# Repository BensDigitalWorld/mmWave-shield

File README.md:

# mmWave-shield

## Wearable mmWave Sensor, for BP measurments. Shield for the BioGap9 Platform 

## Introduction

This repository contains the hardware, firmware, and software developed for a wearable mmWave radar sensing prototype based on the BioGAP platform.

The project integrates a custom BGT60TR13C mmWave radar shield with the BioGAP firmware and provides Python tools for data acquisition, live visualization, offline signal processing, and validation measurements.

The system was developed as a research prototype for contactless pulse-wave sensing using a wearable mmWave radar sensor.

<p align="center">
  <br>
  <em>BioGAP mmWave radar system during validation measurements.</em>
</p>

The prototype includes the following main features:

- Custom mmWave radar shield based on the Infineon BGT60TR13C radar sensor
- Integration with the BioGAP wearable platform
- SPI-based radar control and raw frame readout
- BLE-based command interface and raw radar data streaming
- Python host software for acquisition, live viewing, and offline analysis
- Support for synchronized validation measurements with Finapres/NovaScope reference data
- Mechanical casing files for reproducing the validation setup

## Structure of the Repository

This repository is organized into the following main folders:

```text
Repository/
├── Documentation/
├── Firmware/
├── Hardware/
├── Software/
└── README.md
```

- `Documentation/` contains user documentation, setup instructions, and additional project notes and images.

- `Firmware/` contains the BioGAP firmware extension for the mmWave radar shield. This includes the mmWave application layer, radar control logic, BLE command integration, and firmware configuration changes.

- `Hardware/` contains the hardware design files for the custom mmWave radar shield and the mechanical casing files. This includes KiCad PCB files, fabrication outputs, casing STEP files, and Solid Edge source files.

- `Software/` contains the Python host software for acquisition, live visualization, signal processing, plotting, and validation analysis.

## Usage

For detailed setup and usage instructions, see 

[Getting started FW](Documentation/Firmware/getting_started.md)
[Getting started SW](Software/README.md)

A typical workflow consists of flashing the mmWave firmware, starting the Python host software, recording raw radar data, and processing the measurements offline.

<p align="center">
  <br>
  <em>Python live viewer used to inspect the mmWave radar waveform in real time.</em>
</p>

## Authors

This project was developed at the Integrated Systems Laboratory (IIS) at ETH Zurich.

Main development:

- Benjamin Löliger, ETH Zurich  
  Hardware design, firmware integration, Python software, measurements, signal processing, documentation

Supervision and support:

- Sebastian Frey, ETH Zurich  
  Supervision and project guidance

- Andrea Cossettini, ETH Zurich  
  Supervision and project guidance

- Nima Bahmani, Aalton Finland  
  Supervision and project guidance

## License

The following parts of this repository are released under the Apache License 2.0:

- `Software/`
- `Firmware/`

See the corresponding license files for details: [Software/LICENSE](Software/LICENSE) and [Firmware/LICENSE](Firmware/LICENSE).

The hardware design files are released under the Solderpad Hardware License v0.51:

- `Hardware/`

See [Hardware/LICENSE](Hardware/LICENSE) for details.

This includes the PCB design files as well as the mechanical casing design files, such as STEP and Solid Edge files.

The following documentation images are released under the Creative Commons Attribution 4.0 International License (CC-BY-4.0):

- `Documentation/images/`
- `Hardware/casing/images/`

See the corresponding license files for details: [Documentation/images/LICENSE](Documentation/images/LICENSE) and [Hardware/Casing/images/LICENSE](Hardware/Casing/images/LICENSE).

Some files in the software tools directories contain third-party source code from the Infineon Radar SDK or files based on Infineon example code. Some of these files were adapted for this project.

See the respective source file headers for original copyright notices, modification notes, and license terms.

## Limitation of Liability

The hardware designs, firmware, and software in this repository are provided as-is, without warranty of any kind.

The project is a research prototype and is not intended for medical diagnosis, clinical decision-making, or safety-critical use. The authors and contributors are not liable for any damages or losses arising from the use of this repository, including but not limited to hardware damage, data loss, measurement errors, or incorrect interpretation of results.

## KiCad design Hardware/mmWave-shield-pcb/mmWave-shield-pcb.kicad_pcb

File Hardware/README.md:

# Hardware

## PCB

This directory contains the hardware design files for the custom mmWave radar shield used in this project.

The following PCB project is included:

```text
mmWave-shield-pcb/
```

The PCB was designed in KiCad and contains the schematic, PCB layout, local project libraries, and generated fabrication outputs required to manufacture and assemble the board.

Inside the project folder, you can find the KiCad design files as well as generated documentation and fabrication files such as schematics, bill of materials, Gerber files, and 3D model exports.

## Casing

In the folder Casing you can find .stl files for a 3d printed casing model that can be used with the BioGap + mmWave Shield. 

## License

The hardware source design files are licensed under the Solderpad Hardware License v0.51. See `Hardware/LICENSE` for details.

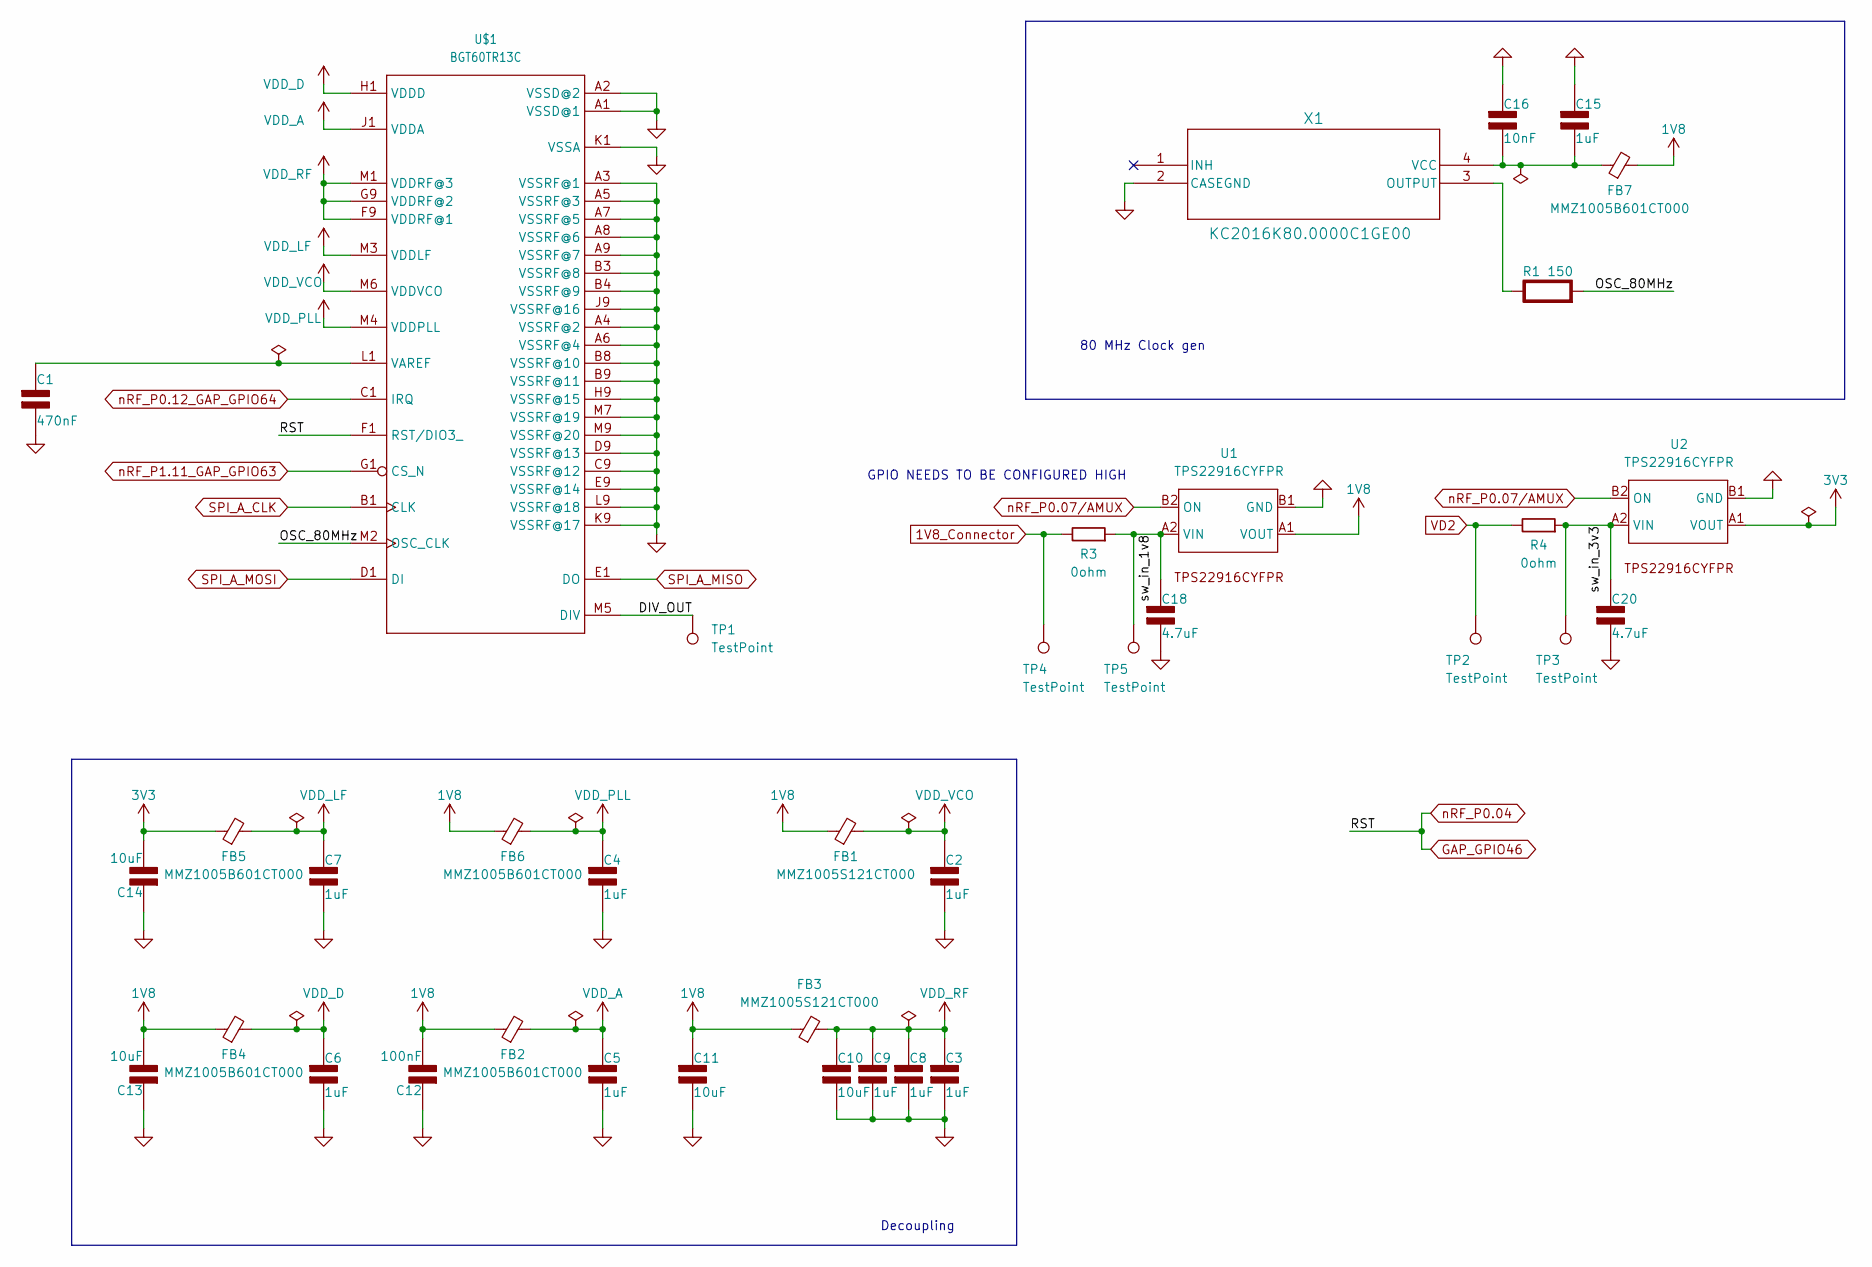
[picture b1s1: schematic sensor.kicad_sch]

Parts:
C1: 470nF; C_0402_1005Metric; Rating V
C2, C3, C4, C5, C6, C7, C8, C9, C15: 1uF; C_0402_1005Metric; Rating V
C10, C11, C13, C14: 10uF; C_0402_1005Metric; Rating V
C12: 100nF; C_0402_1005Metric; Rating V
C16: 10nF; C_0402_1005Metric; Rating V
C18, C20: 4.7uF; C_0402_1005Metric; Rating V
FB1, FB3: MMZ1005S121CT000; IND_1005_TDK-L
FB2, FB4, FB5, FB6, FB7: MMZ1005B601CT000; IND_1005_TDK-L
R1: 150; R_0402_1005Metric; Rating W
R3, R4: 0ohm; R_0805_2012Metric
TP1, TP2, TP3, TP4, TP5: TestPoint; TestPoint_Pad_D1.0mm
U1, U2: TPS22916CYFPR
U$1: BGT60TR13C; BGA40N50P9X12_500X650X90-V
X1: KC2016K80.0000C1GE00; KC2016K_KYO

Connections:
1V8: C11.1 (+), C12.2 (-), C13.2 (-), FB1.1, FB2.1, FB3.1, FB4.1, FB6.1, FB7.2, U1.A1 (VOUT)
1V8_Connector: R3.2, TP4.1; also elsewhere on the board
3V3: C14.2 (-), FB5.1, U2.A1 (VOUT)
/sensor/DIV_OUT: TP1.1, U$1.M5 (DIV); also elsewhere on the board
/sensor/OSC_80MHz: R1.2 (-), U$1.M2 (OSC_CLK)
/sensor/sw_in_1v8: C18.1 (+), R3.1, TP5.1, U1.A2 (VIN)
/sensor/sw_in_3v3: C20.1 (+), R4.1, TP3.1, U2.A2 (VIN)
GAP_GPIO46: U$1.F1 (RST/DIO3_); also elsewhere on the board
GND: C1.2 (-), C2.2 (-), C3.2 (-), C4.2 (-), C5.2 (-), C6.2 (-), C7.2 (-), C8.2 (-), C9.2 (-), C10.2 (-), C11.2 (-), C12.1 (+), C13.1 (+), C14.1 (+), C15.1 (+), C16.1 (+), C18.2 (-), C20.2 (-), U1.B1 (GND), U2.B1 (GND), U$1.A1 (VSSD@1), U$1.A2 (VSSD@2), U$1.A3 (VSSRF@1), U$1.A4 (VSSRF@2), U$1.A5 (VSSRF@3), U$1.A6 (VSSRF@4), U$1.A7 (VSSRF@5), U$1.A8 (VSSRF@6), U$1.A9 (VSSRF@7), U$1.B3 (VSSRF@8), U$1.B4 (VSSRF@9), U$1.B8 (VSSRF@10), U$1.B9 (VSSRF@11), U$1.C9 (VSSRF@12), U$1.D9 (VSSRF@13), U$1.E9 (VSSRF@14), U$1.H9 (VSSRF@15), U$1.J9 (VSSRF@16), U$1.K1 (VSSA), U$1.K9 (VSSRF@17), U$1.L9 (VSSRF@18), U$1.M7 (VSSRF@19), U$1.M9 (VSSRF@20), X1.2 (CASEGND); also elsewhere on the board
unnamed: C1.1 (+), U$1.L1 (VAREF)
unnamed: C15.2 (-), C16.2 (-), FB7.1, X1.4 (VCC)
unnamed: R1.1 (+), X1.3 (OUTPUT)
SPI_A_CLK: U$1.B1 (CLK); also elsewhere on the board
SPI_A_MISO: U$1.E1 (DO); also elsewhere on the board
SPI_A_MOSI: U$1.D1 (DI); also elsewhere on the board
VD2: R4.2, TP2.1; also elsewhere on the board
VDD_A: C5.1 (+), FB2.2, U$1.J1 (VDDA)
VDD_D: C6.1 (+), FB4.2, U$1.H1 (VDDD)
VDD_LF: C7.1 (+), FB5.2, U$1.M3 (VDDLF)
VDD_PLL: C4.1 (+), FB6.2, U$1.M4 (VDDPLL)
VDD_RF: C3.1 (+), C8.1 (+), C9.1 (+), C10.1 (+), FB3.2, U$1.F9 (VDDRF@1), U$1.G9 (VDDRF@2), U$1.M1 (VDDRF@3)
VDD_VCO: C2.1 (+), FB1.2, U$1.M6 (VDDVCO)
nRF_P0.07/AMUX: U1.B2 (ON), U2.B2 (ON); also elsewhere on the board
nRF_P0.12_GAP_GPIO64: U$1.C1 (IRQ); also elsewhere on the board
nRF_P1.11_GAP_GPIO63: U$1.G1 (CS_N); also elsewhere on the board

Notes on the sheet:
80 MHz Clock gen
GPIO NEEDS TO BE CONFIGURED HIGH
Decoupling

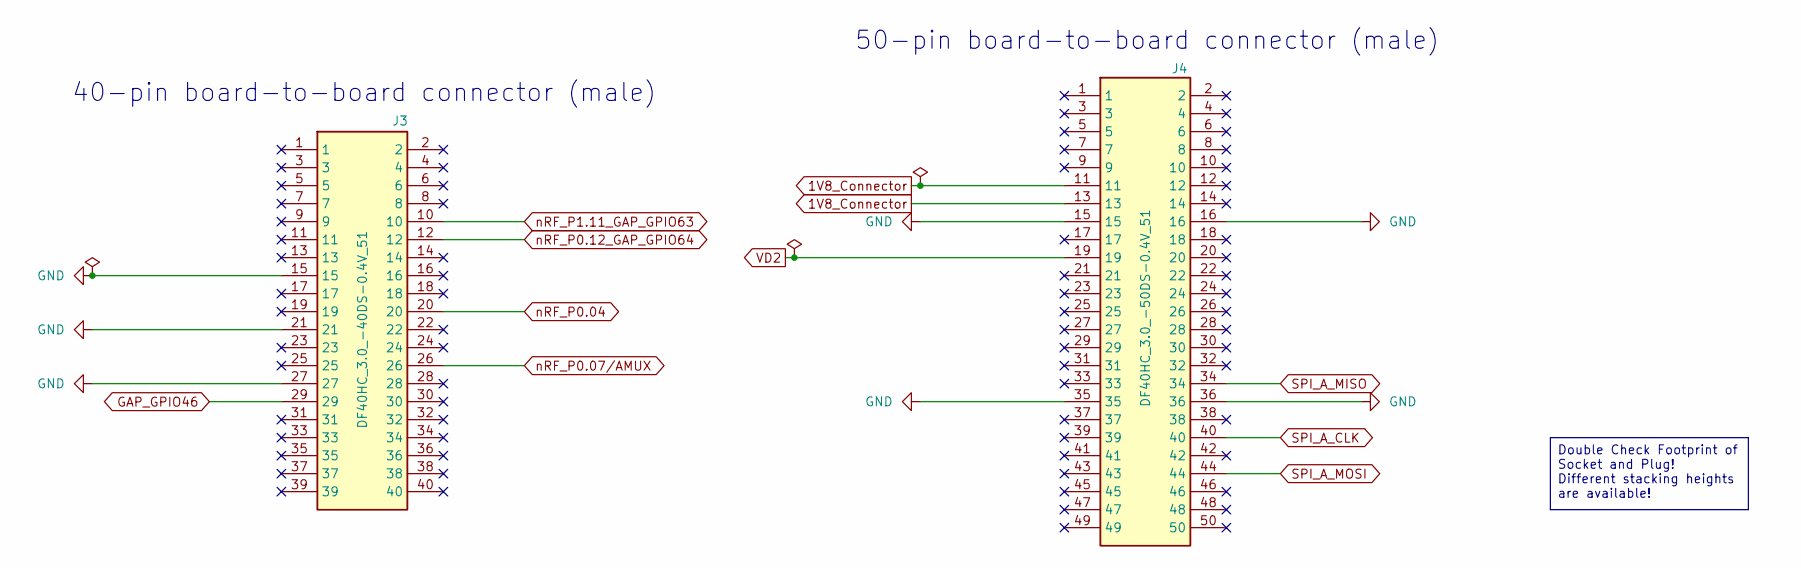
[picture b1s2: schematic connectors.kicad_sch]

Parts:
J3: DF40HC_3.0_-40DS-0.4V_51; Hirose_DF40HC(3.0)-40DS-0.4V_2x20_P0.4mm; Mouser Part Number 798-DF40HC3040DS04V5
J4: DF40HC_3.0_-50DS-0.4V_51; Hirose_DF40HC(3.0)-50DS-0.4V_2x25_P0.4mm; Mouser Part Number 798-DF40HC3050DS04V

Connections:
1V8_Connector: J4.11, J4.13; also elsewhere on the board
GAP_GPIO46: J3.20, J3.29; also elsewhere on the board
GND: J3.15, J3.21, J3.27, J4.15, J4.16, J4.35, J4.36; also elsewhere on the board
SPI_A_CLK: J4.40; also elsewhere on the board
SPI_A_MISO: J4.34; also elsewhere on the board
SPI_A_MOSI: J4.44; also elsewhere on the board
VD2: J4.19; also elsewhere on the board
nRF_P0.07/AMUX: J3.26; also elsewhere on the board
nRF_P0.12_GAP_GPIO64: J3.12; also elsewhere on the board
nRF_P1.11_GAP_GPIO63: J3.10; also elsewhere on the board

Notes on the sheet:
50-pin board-to-board connector (male)
40-pin board-to-board connector (male)
Double Check Footprint of Socket and Plug! Different stacking heights are available!

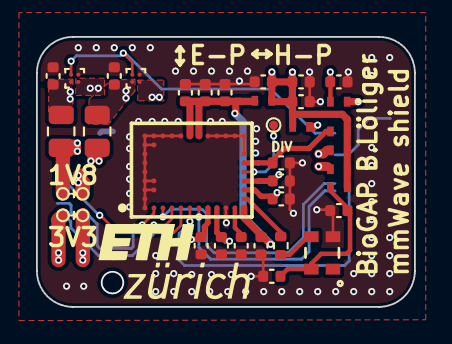
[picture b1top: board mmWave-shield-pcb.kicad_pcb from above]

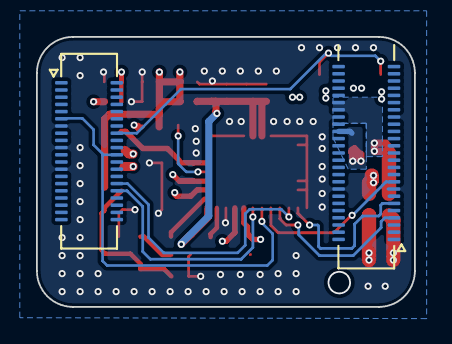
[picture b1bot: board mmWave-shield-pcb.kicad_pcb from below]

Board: 4 copper layers, 21.0 x 15.0 mm, 39 parts (2 on the bottom side), 25 nets.

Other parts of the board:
DIV: TestPoint; TestPoint_Pad_D1.0mm

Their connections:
/sensor/DIV_OUT: DIV.1; also elsewhere on the board

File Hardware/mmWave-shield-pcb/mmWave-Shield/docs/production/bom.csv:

Designator,Footprint,Quantity,Value,LCSC Part #
C1,0402,1,470nF,
"C10, C11, C13, C14",0402,4,10uF,
C12,0402,1,100nF,
"C15, C2, C3, C4, C5, C6, C7, C8, C9",0402,9,1uF,
C16,0402,1,10nF,
"FB1, FB3",IND_1005_TDK-L,2,MMZ1005S121CT000,
"FB2, FB4, FB5, FB6, FB7",IND_1005_TDK-L,5,MMZ1005B601CT000,
J3,Hirose_DF40HC(3.0)-40DS-0.4V_2x20_P0.4mm,1,DF40HC_3.0_-40DS-0.4V_51,
J4,Hirose_DF40HC(3.0)-50DS-0.4V_2x25_P0.4mm,1,DF40HC_3.0_-50DS-0.4V_51,
R1,0402,1,150,
TP1,TestPoint_Pad_D1.0mm,1,TestPoint,
U$1,BGA40N50P9X12_500X650X90-V,1,BGT60TR13C,
U1,KC2016K_KYO,1,KC2016K80.0000C1GE00,

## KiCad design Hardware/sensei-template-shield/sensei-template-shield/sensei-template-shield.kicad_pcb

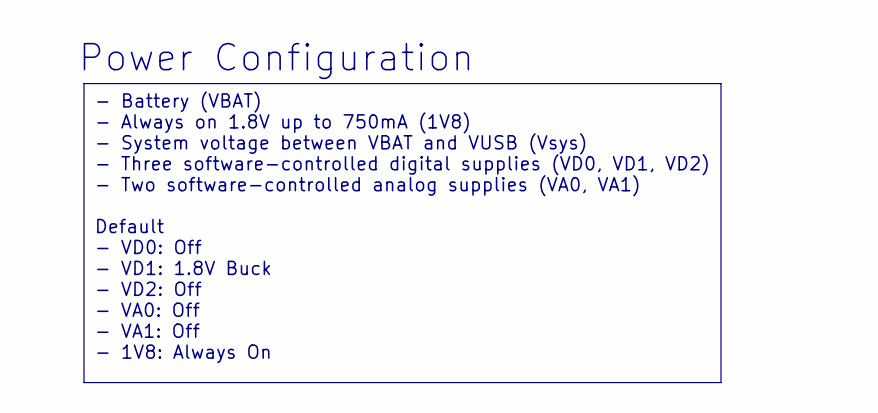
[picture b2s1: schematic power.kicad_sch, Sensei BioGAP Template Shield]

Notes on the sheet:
Power Configuration
- Battery (VBAT) - Always on 1.8V up to 750mA (1V8) - System voltage between VBAT and VUSB (Vsys) - Three software-controlled digital supplies (VD0, VD1, VD2) - Two software-controlled analog supplies (VA0, VA1) Default - VD0: Off - VD1: 1.8V Buck - VD2: Off - VA0: Off - VA1: Off - 1V8: Always On

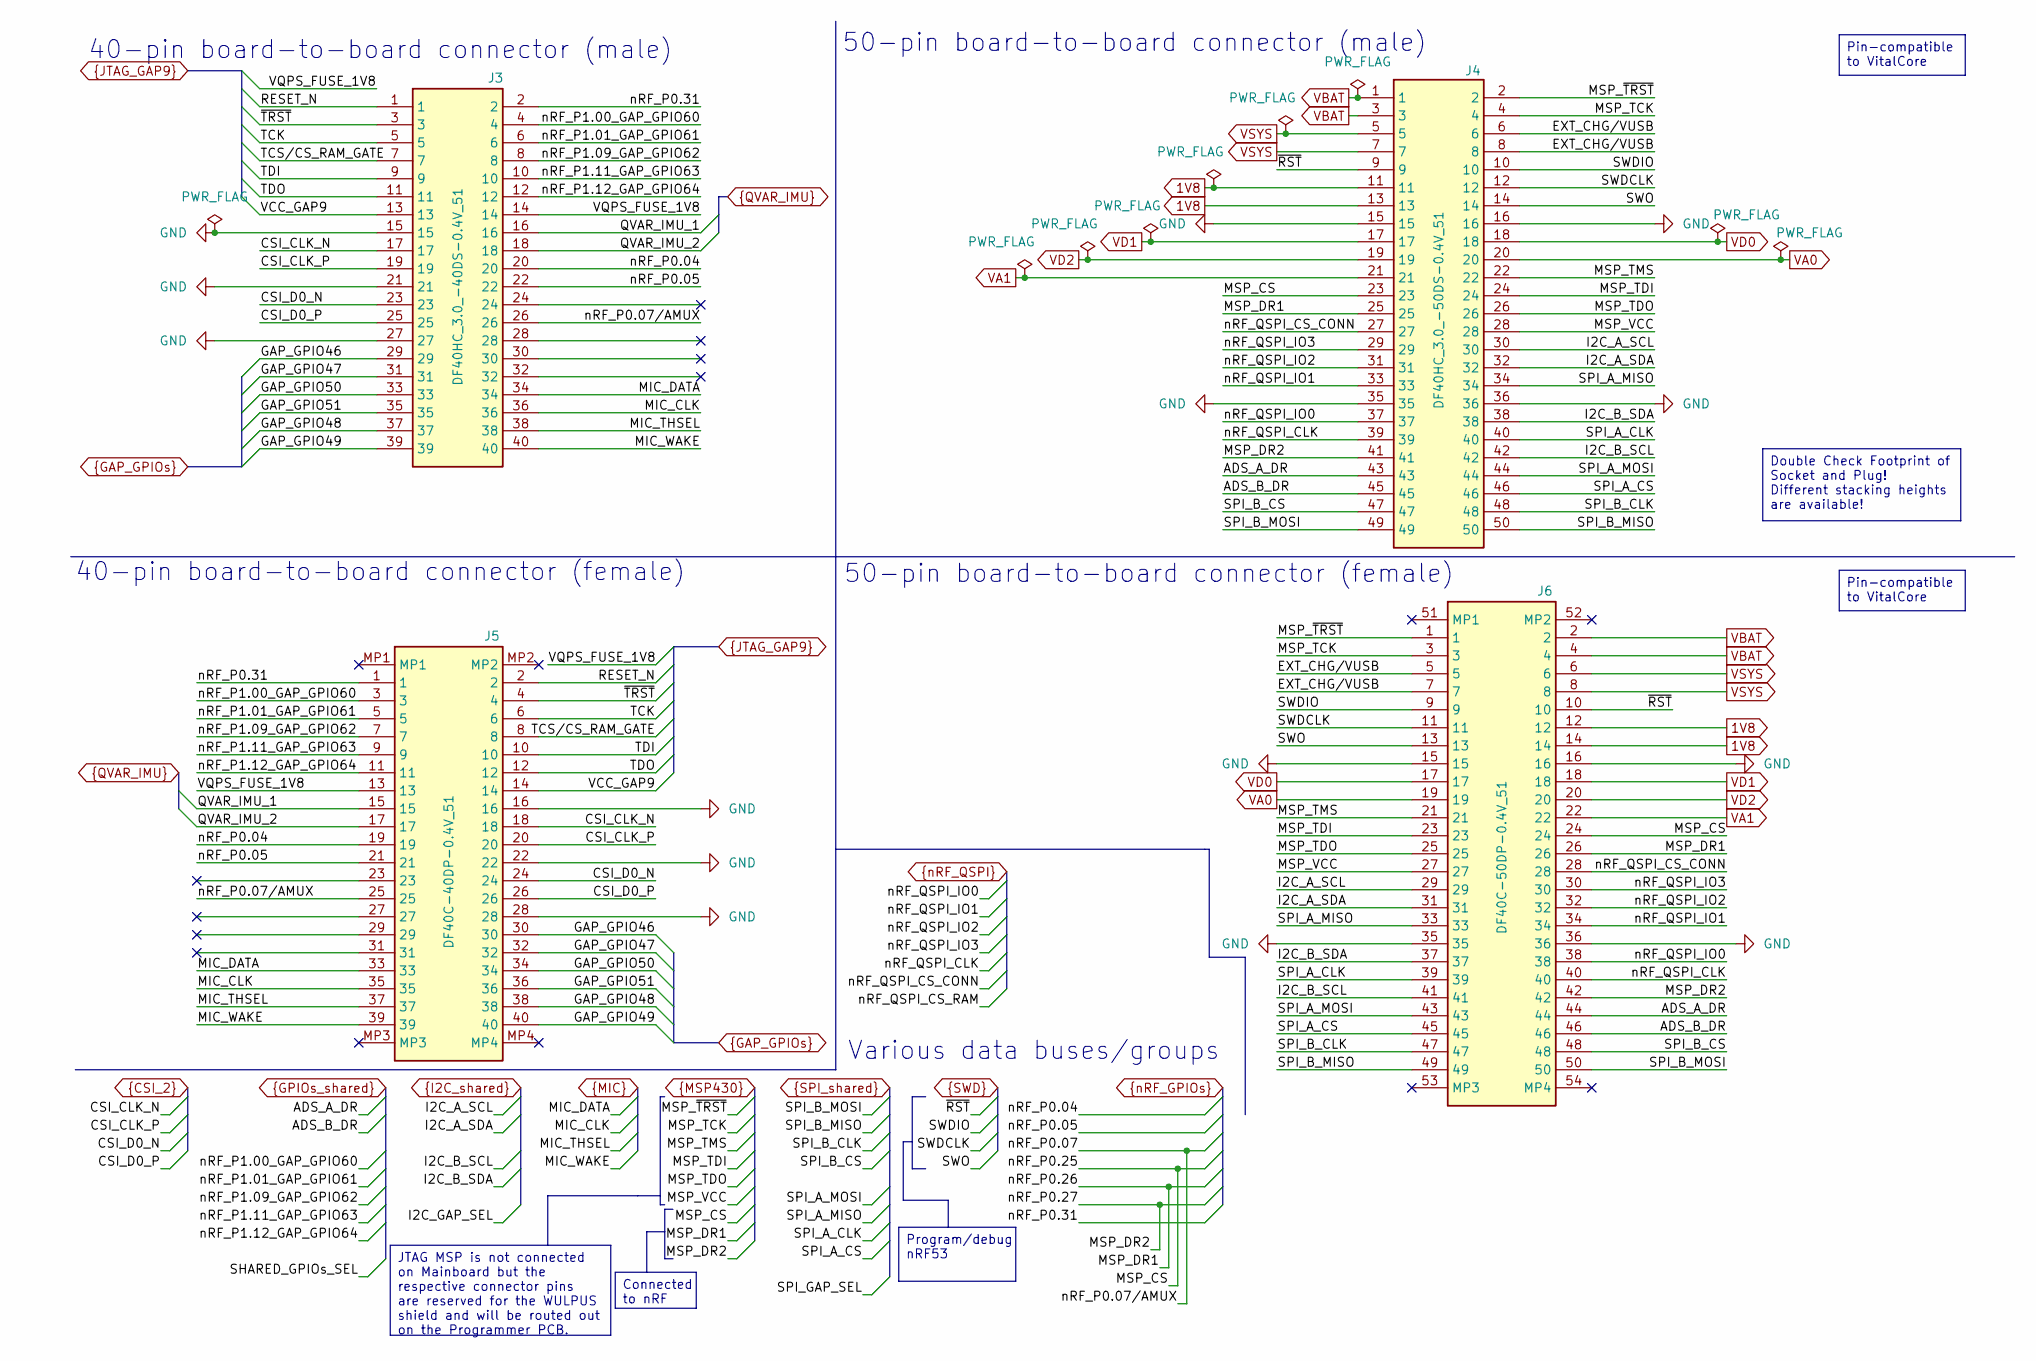
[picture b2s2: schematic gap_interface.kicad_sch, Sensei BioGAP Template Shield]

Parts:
J3: DF40HC_3.0_-40DS-0.4V_51; DF40HC3040DS04V51; Mouser Part Number 798-DF40HC3040DS04V5
J4: DF40HC_3.0_-50DS-0.4V_51; DF40HC3050DS04V51; Mouser Part Number 798-DF40HC3050DS04V
J5: DF40C-40DP-0.4V_51; DF40C40DP04V51; Mouser Part Number 798-DF40C40DP0.4V51
J6: DF40C-50DP-0.4V_51; DF40C50DP04V51; Mouser Part Number 798-DF40C50DP0.4V51

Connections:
1V8: J4.11, J4.13, J6.12, J6.14
/GAP Interface/EXT_CHG/VUSB: J4.6, J4.8, J6.5, J6.7
ADS_A_DR: J4.43, J6.44
ADS_B_DR: J4.45, J6.46
CSI_CLK_N: J3.17, J5.18
CSI_CLK_P: J3.19, J5.20
CSI_D0_N: J3.23, J5.24
CSI_D0_P: J3.25, J5.26
GAP_GPIO46: J3.29, J5.30
GAP_GPIO47: J3.31, J5.32
GAP_GPIO48: J3.37, J5.38
GAP_GPIO49: J3.39, J5.40
GAP_GPIO50: J3.33, J5.34
GAP_GPIO51: J3.35, J5.36
GND: J3.15, J3.21, J3.27, J4.15, J4.16, J4.35, J4.36, J5.16, J5.22, J5.28, J6.15, J6.16, J6.35, J6.36
I2C_A_SCL: J4.30, J6.29
I2C_A_SDA: J4.32, J6.31
I2C_B_SCL: J4.42, J6.41
I2C_B_SDA: J4.38, J6.37
MIC_CLK: J3.36, J5.35
MIC_DATA: J3.34, J5.33
MIC_THSEL: J3.38, J5.37
MIC_WAKE: J3.40, J5.39
MSP_CS: J4.23, J6.24
MSP_DR1: J4.25, J6.26
MSP_DR2: J4.41, J6.42
MSP_TCK: J4.4, J6.3
MSP_TDI: J4.24, J6.23
MSP_TDO: J4.26, J6.25
MSP_TMS: J4.22, J6.21
MSP_VCC: J4.28, J6.27
MSP_~TRST: J4.2, J6.1
QVAR_IMU_1: J3.16, J5.15
QVAR_IMU_2: J3.18, J5.17
RESET_N: J3.1, J5.2
SPI_A_CLK: J4.40, J6.39
SPI_A_CS: J4.46, J6.45
SPI_A_MISO: J4.34, J6.33
SPI_A_MOSI: J4.44, J6.43
SPI_B_CLK: J4.48, J6.47
SPI_B_CS: J4.47, J6.48
SPI_B_MISO: J4.50, J6.49
SPI_B_MOSI: J4.49, J6.50
SWDCLK: J4.12, J6.11
SWDIO: J4.10, J6.9
SWO: J4.14, J6.13
TCK: J3.5, J5.6
TCS/CS_RAM_GATE: J3.7, J5.8
TDI: J3.9, J5.10
TDO: J3.11, J5.12
VA0: J4.20, J6.19
VA1: J4.21, J6.22
VBAT: J4.1, J4.3, J6.2, J6.4
VCC_GAP9: J3.13, J5.14
VD0: J4.18, J6.17
VD1: J4.17, J6.18
VD2: J4.19, J6.20
VQPS_FUSE_1V8: J3.14, J5.13
VSYS: J4.5, J4.7, J6.6, J6.8
nRF_P0.04: J3.20, J5.19
nRF_P0.05: J3.22, J5.21
nRF_P0.07: J3.26, J5.25
nRF_P0.31: J3.2, J5.1
nRF_P1.00_GAP_GPIO60: J3.4, J5.3
nRF_P1.01_GAP_GPIO61: J3.6, J5.5
nRF_P1.09_GAP_GPIO62: J3.8, J5.7
nRF_P1.11_GAP_GPIO63: J3.10, J5.9
nRF_P1.12_GAP_GPIO64: J3.12, J5.11
nRF_QSPI_CLK: J4.39, J6.40
nRF_QSPI_CS_CONN: J4.27, J6.28
nRF_QSPI_IO0: J4.37, J6.38
nRF_QSPI_IO1: J4.33, J6.34
nRF_QSPI_IO2: J4.31, J6.32
nRF_QSPI_IO3: J4.29, J6.30
~RST: J4.9, J6.10
~TRST: J3.3, J5.4

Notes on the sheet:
Various data buses/groups
40-pin board-to-board connector (female)
40-pin board-to-board connector (male)
50-pin board-to-board connector (female)
50-pin board-to-board connector (male)
Program/debug nRF53
Pin-compatible to VitalCore
Double Check Footprint of Socket and Plug! Different stacking heights are available!
Connected to nRF
JTAG MSP is not connected on Mainboard but the respective connector pins are reserved for the WULPUS shield and will be routed out on the Programmer PCB.

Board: 6 copper layers, 4 parts (2 on the bottom side), 76 nets, no tracks yet.

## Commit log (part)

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2026-03-02 adding first folders
2026-03-15 kicad project inital version
2026-03-15 arranged components on pcb
2026-03-15 update git ignore
2026-03-16 ignore template folders
2026-03-16 working on scematic1
2026-03-17 Placed Connectors in hopefully right way
2026-03-17 exported 3d model
2026-03-20 small changes scematic
2026-03-20 adjustments
2026-03-22 V1 of pcb layout
2026-03-23 added some docs fpr the pcb
2026-03-23 small adjustments
2026-03-23 finished adding power controll
2026-03-24 Cleaning up a bit
2026-03-24 changed schema
2026-03-24 Removed cap and rerouted some power lines
2026-03-25 added 3d models for new components
2026-03-25 updated BoM
2026-03-27 Final Touches and genertated fabrication files
2026-03-27 added part ordering list
2026-06-10 Uploaded FW, added getting started
2026-06-10 git ignore for HW
2026-06-10 updated ignore me
2026-06-10 cleaning up HW folder1
2026-06-10 cleanign up HW folder2
2026-06-11 Finish up HW cleaning
2026-06-12 first upload python scripts
2026-06-30 added header and read me software/HW
